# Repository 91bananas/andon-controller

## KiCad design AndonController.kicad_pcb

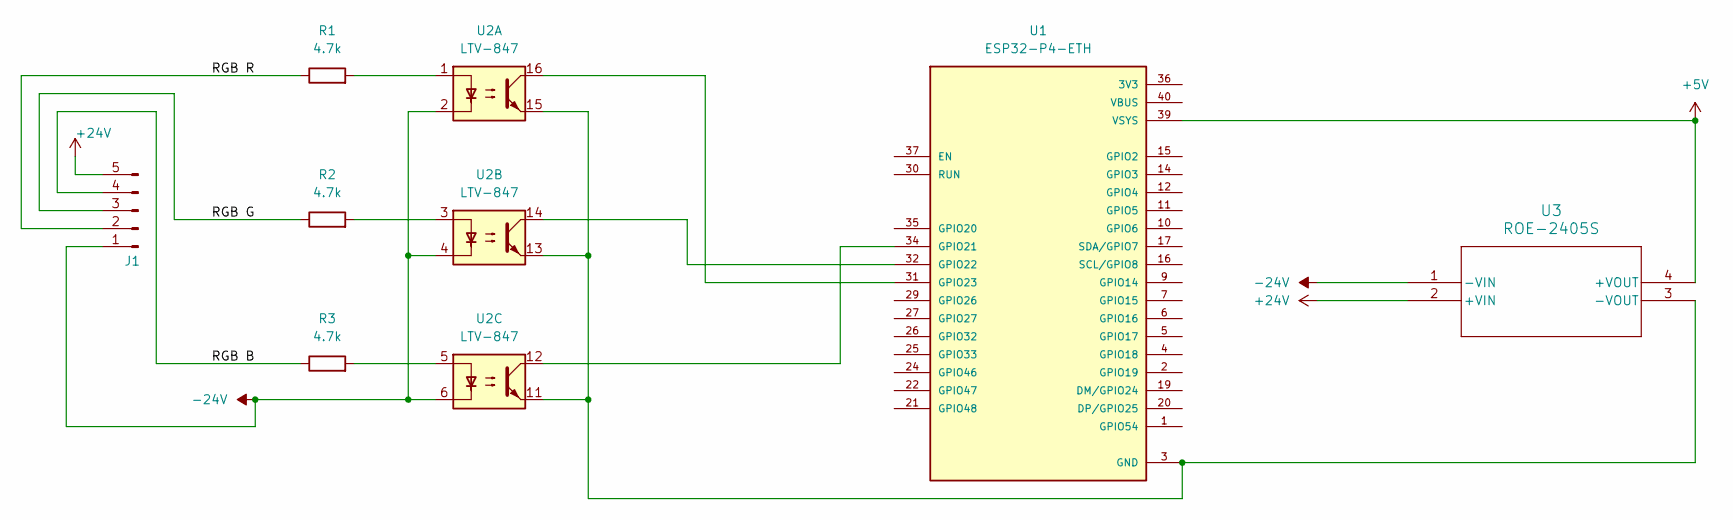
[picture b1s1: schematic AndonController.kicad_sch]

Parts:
J1: Conn_01x05_Pin; PhoenixContact_MSTBA_2,5_5-G-5,08_1x05_P5.08mm_Horizontal
R1, R2, R3: 4.7k; R_Axial_DIN0207_L6.3mm_D2.5mm_P10.16mm_Horizontal
U1: ESP32-P4-ETH; MODULE_ESP32-P4-ETH
U2: LTV-847; DIP-16_W7.62mm
U3: ROE-2405S; ROE_RCP

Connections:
+5V: U1.39 (VSYS), U3.4 (+VOUT)
+24V: J1.5, U3.2 (+VIN)
-24V: J1.1, U2.2, U2.4, U2.6, U3.1 (-VIN)
/RGB B: J1.4, R3.1
/RGB G: J1.3, R2.1
/RGB R: J1.2, R1.1
GND: U1.3 (GND), U1.8 (GND), U1.13 (GND), U1.18 (GND), U1.23 (GND), U1.28 (GND), U1.33 (GND), U1.38 (GND), U2.11, U2.13, U2.15, U3.3 (-VOUT)
unnamed: R1.2, U2.1
unnamed: R2.2, U2.3
unnamed: R3.2, U2.5
unnamed: U1.34 (GPIO21), U2.12
unnamed: U1.32 (GPIO22), U2.14
unnamed: U1.31 (GPIO23), U2.16

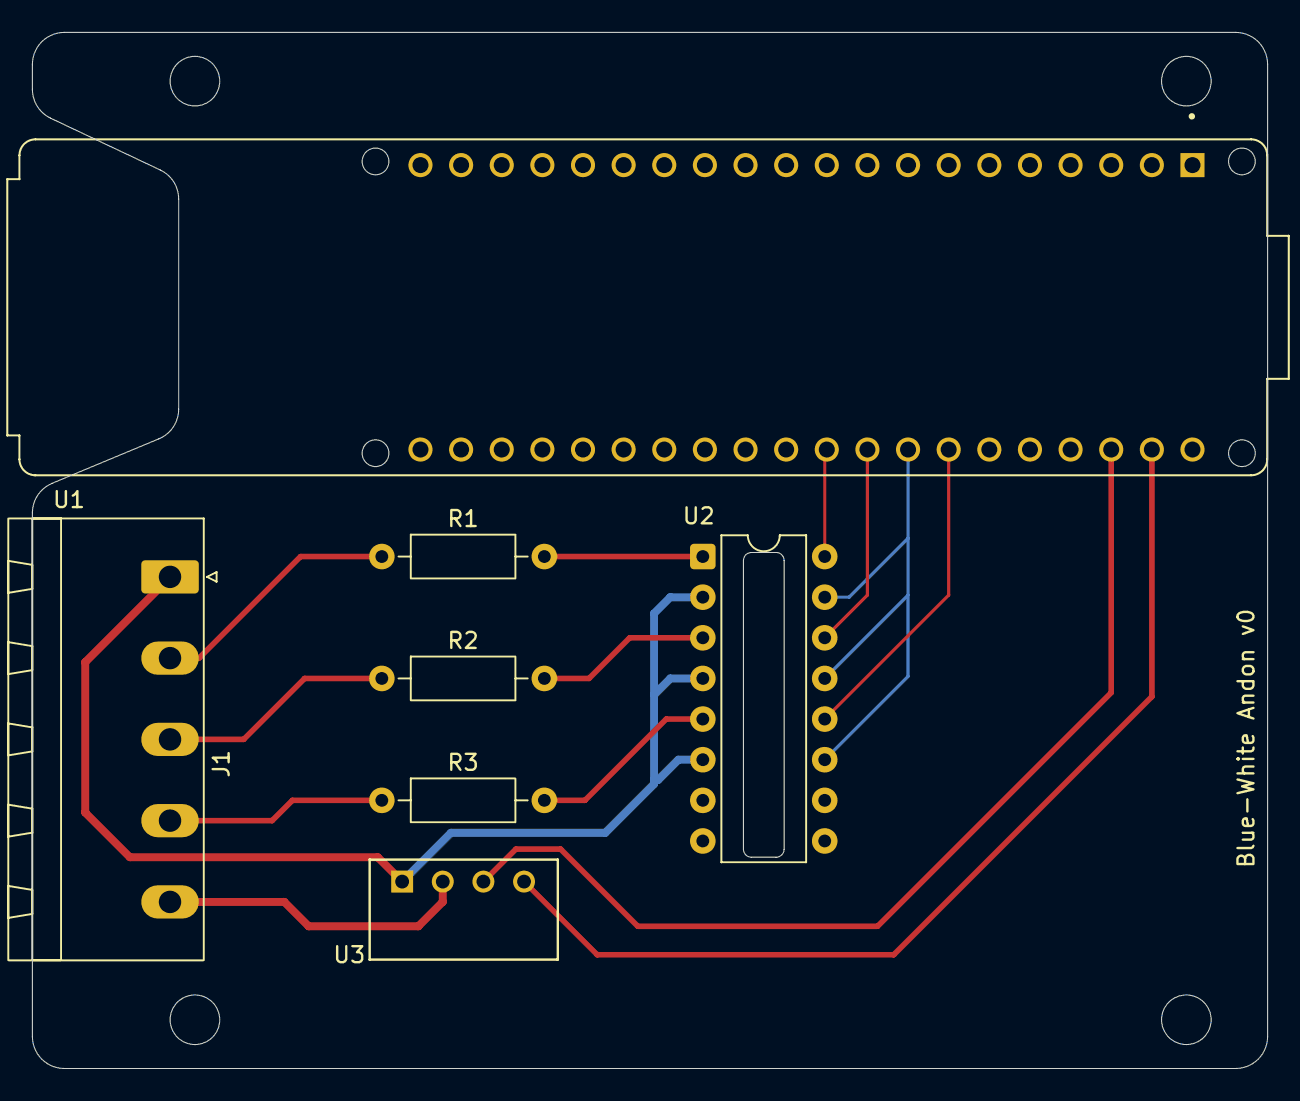
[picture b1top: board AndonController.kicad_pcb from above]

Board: 2 copper layers, 77.2 x 64.8 mm, 7 parts (0 on the bottom side), 13 nets.
